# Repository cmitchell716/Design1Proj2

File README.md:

# Design1Proj2
This repository holds the source code for ECEN 4013 Group 2 Project 2.
The PCB and Case directories hold the files required for each component respectively. 
The headers directory have the modified header files in order to save memory.
Sketches hold all code run on the arduino, project_full is the final sketch used in the 
demonstration. All others test individual components or other related activities.

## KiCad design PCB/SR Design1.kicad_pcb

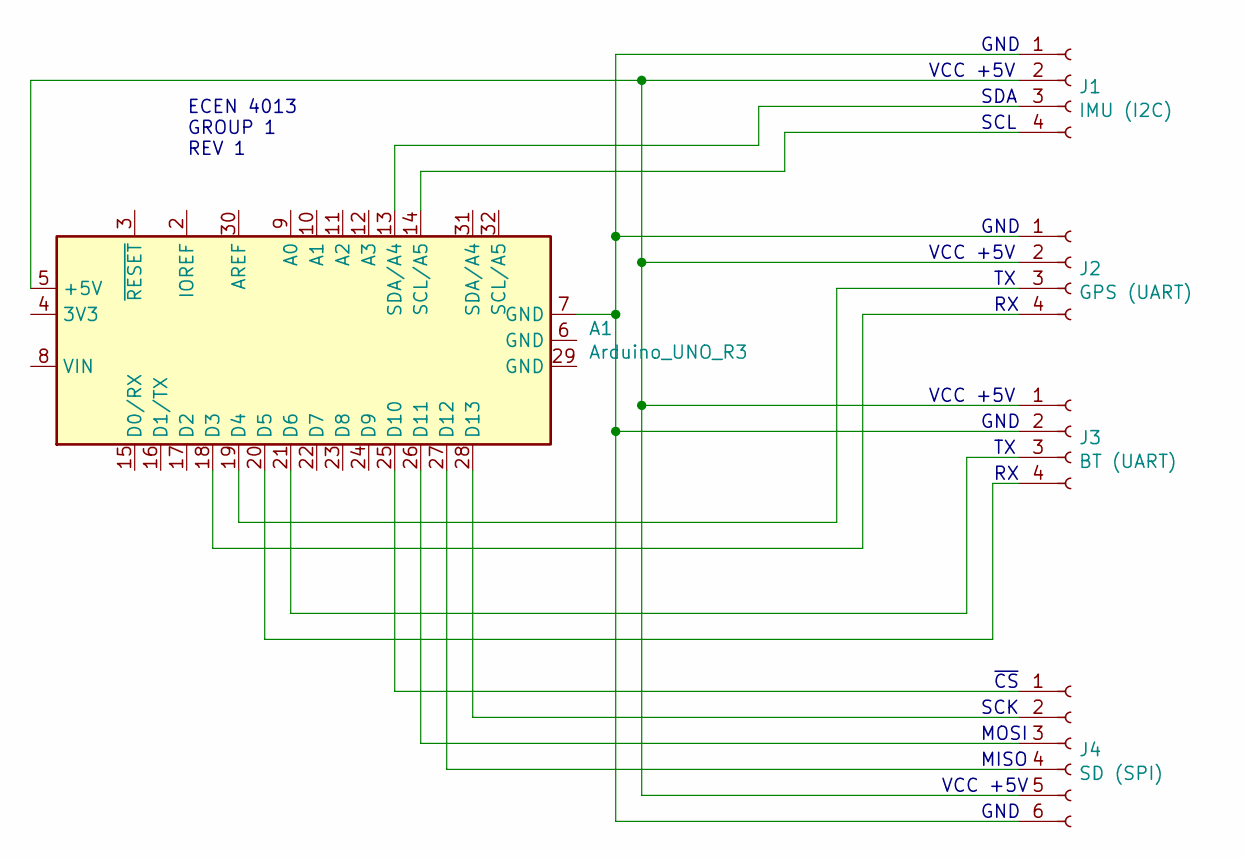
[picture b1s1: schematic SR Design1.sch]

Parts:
A1: Arduino_UNO_R3
J1: IMU (I2C); PinHeader_1x04_P1.00mm_Horizontal
J2: GPS (UART); PinHeader_1x04_P1.00mm_Horizontal
J3: BT (UART); PinSocket_1x04_P2.54mm_Horizontal
J4: SD (SPI); PinSocket_1x06_P2.54mm_Horizontal

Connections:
unnamed: A1.5 (+5V), J1.2, J2.2, J3.1, J4.5
unnamed: A1.7 (GND), J1.1, J2.1, J3.2, J4.6
unnamed: A1.13 (SDA/A4), J1.3
unnamed: A1.14 (SCL/A5), J1.4
unnamed: A1.18 (D3), J2.4
unnamed: A1.19 (D4), J2.3
unnamed: A1.20 (D5), J3.4
unnamed: A1.21 (D6), J3.3
unnamed: A1.25 (D10), J4.1
unnamed: A1.26 (D11), J4.3
unnamed: A1.27 (D12), J4.4
unnamed: A1.28 (D13), J4.2

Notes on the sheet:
GND
VCC +5V
SDA
SCL
SCK
MOSI
MISO
~CS
ECEN 4013 GROUP 1 REV 1

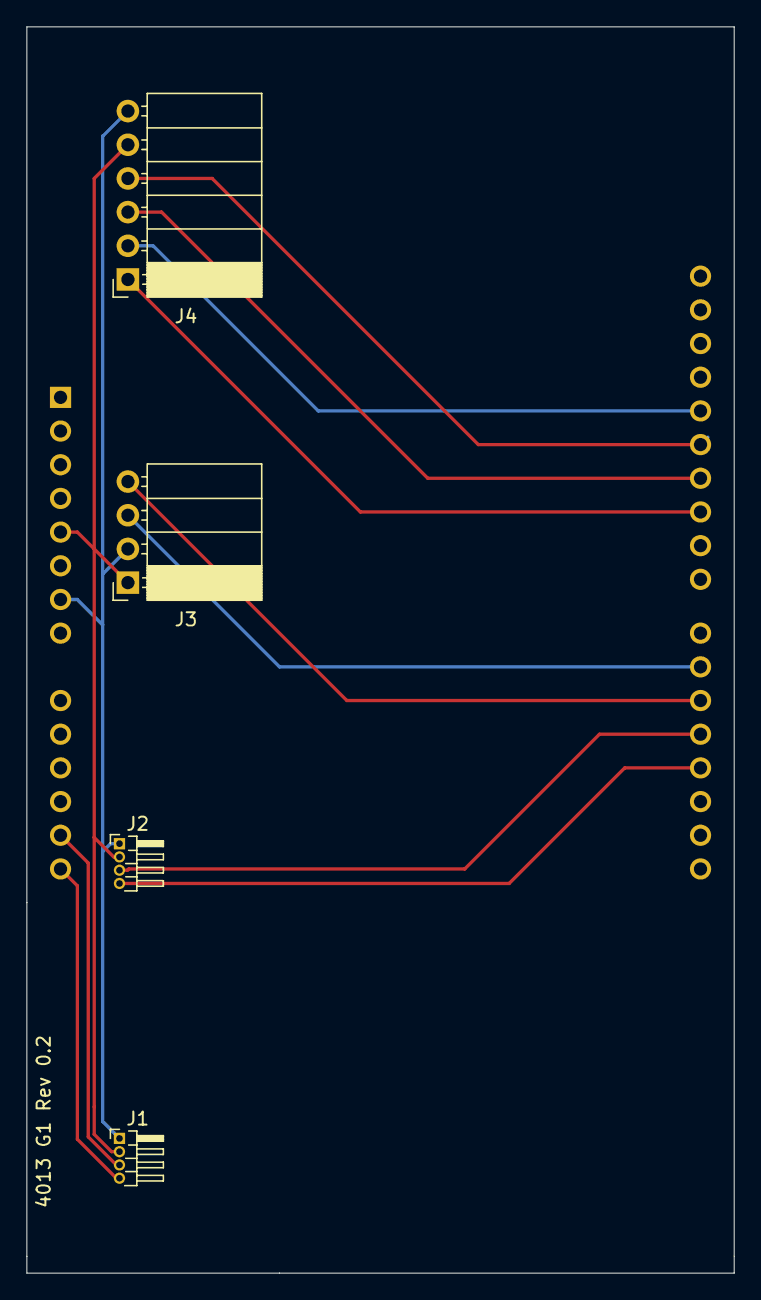
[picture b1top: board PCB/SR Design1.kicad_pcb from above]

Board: 2 copper layers, 53.3 x 94.0 mm, 5 parts (1 on the bottom side), 12 nets.

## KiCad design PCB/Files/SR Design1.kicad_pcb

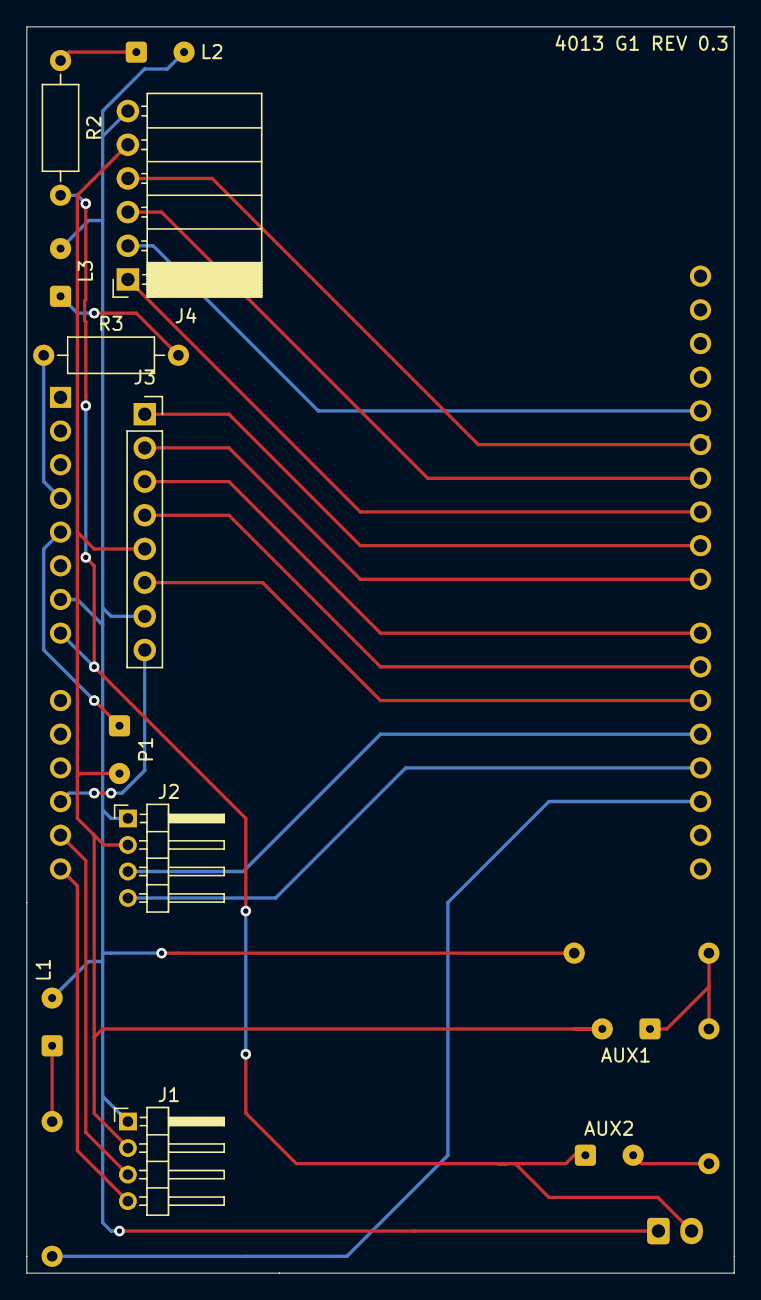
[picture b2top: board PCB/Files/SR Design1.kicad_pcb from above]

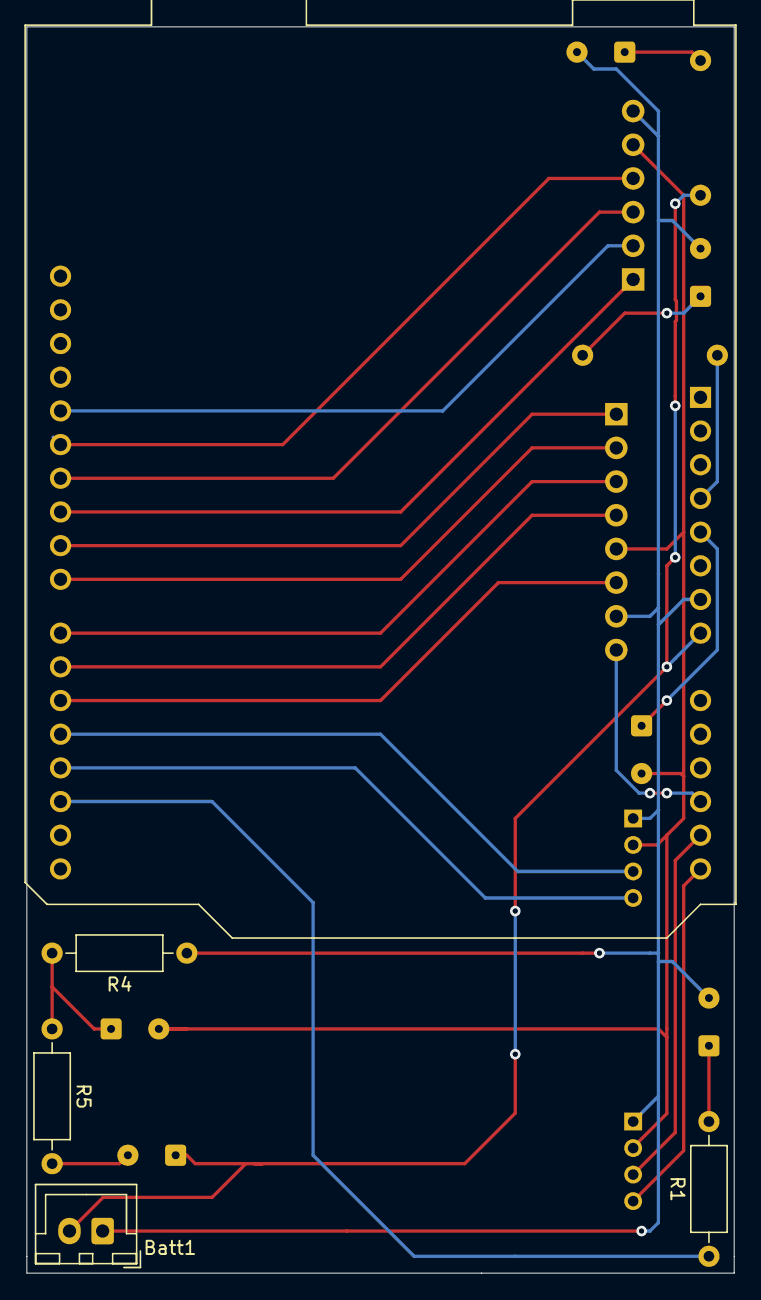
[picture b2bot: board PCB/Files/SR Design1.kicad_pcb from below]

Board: 2 copper layers, 53.3 x 94.0 mm, 17 parts (5 on the bottom side), 25 nets.

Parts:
A1: Arduino_UNO_R3
AUX1, AUX2: PWR; SolderWire-0.1sqmm_1x02_P3.6mm_D0.4mm_OD1mm
Batt1: PWR; JST_XH_B2B-XH-A_1x02_P2.50mm_Vertical
J1: IMU (I2C); PinHeader_1x04_P2.00mm_Horizontal
J2: GPS (UART); PinHeader_1x04_P2.00mm_Horizontal
J3: BT (UART +); PinSocket_1x08_P2.54mm_Vertical
J4: SD (SPI); PinSocket_1x06_P2.54mm_Horizontal
L1, L2, L3: LED; SolderWire-0.1sqmm_1x02_P3.6mm_D0.4mm_OD1mm
P1: PWR; SolderWire-0.1sqmm_1x02_P3.6mm_D0.4mm_OD1mm
R1, R2, R3: R227; R_Axial_DIN0207_L6.3mm_D2.5mm_P10.16mm_Horizontal
R4: R5k; R_Axial_DIN0207_L6.3mm_D2.5mm_P10.16mm_Horizontal
R5: R2.2k; R_Axial_DIN0207_L6.3mm_D2.5mm_P10.16mm_Horizontal

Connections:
unnamed: A1.4, R3.1
unnamed: A1.5, P1.1
unnamed: A1.7, Batt1.1, J1.1, J2.1, J3.7, J4.6, L1.2, L2.2, L3.2, R4.1
unnamed: A1.8, AUX2.1, Batt1.2, R2.1
unnamed: A1.12, J3.8
unnamed: A1.13, J1.3
unnamed: A1.14, J1.4
unnamed: A1.17, R1.1
unnamed: A1.18, J2.4
unnamed: A1.19, J2.3
unnamed: A1.20, J3.6
unnamed: A1.21, J3.4
unnamed: A1.22, J3.3
unnamed: A1.23, J3.2
unnamed: A1.24, J3.1
unnamed: A1.25, J4.1
unnamed: A1.26, J4.3
unnamed: A1.27, J4.4
unnamed: A1.28, J4.2
unnamed: AUX1.1, R4.2, R5.1
unnamed: AUX1.2, J1.2, J2.2, J3.5, J4.5, P1.2
unnamed: AUX2.2, R5.2
unnamed: L1.1, R1.2
unnamed: L2.1, R2.2
unnamed: L3.1, R3.2

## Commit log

2021-11-01 Adding PCB Files and Dir
    Adding the KiCad Files and supplementary file structure (Currently Using SVN - Trunk, Branch, Tag Structure. Can be changed later)
2021-11-02 add BT test sketch
2021-11-02 Revert "Adding PCB Files and Dir"
    This reverts commit 94645a1b65692bb09303bc4e4d5ecebb7ac4a380.
2021-11-03 Adding PCB Files
    Adds
    - fp-info-cache
    - Sr Design 1-cache.lib
    - Sr Design 1.kicad_pcb
    - Sr Design 1.kicad_pcb-bak
    - Sr Design 1.net
2021-11-03 IMU test, configuration, and I2C connection check
2021-11-03 Updated PCB to REV 0.3
    Updated all PCB files previously added. These should be updated to Rev 0.3 with new BT module and alternative power circuit. Board size not changed.
2021-11-03 Updated Schmatic
    Updated Schematic to the correct revision.
2021-11-04 Adding finished PCB and Gerber Files
    Added all Gerber files not in .zip form. Also updated PCB to newest version.
2021-11-05 GPS and Combined Input
2021-11-05 Added sd_test
2021-11-06 reduced storage space of IMU and fixed magnetometer
2021-11-09 strip header files for full sketch
2021-11-09 Changed buffer size for SD to 256
    To change the buffer further, look at lines 69 and 182.
2021-11-10 project_full outputs blutooth and serial
2021-11-12 Adding Case Files
    Adding SolidWorks files and STL files of our case.
2021-11-12 full implementation without testing bluetooth
2021-11-15 Bluetooth working with some data loss
2021-11-16 final code fingers crossed
2021-11-17 Update fp-info-cache
2021-11-17 Moved KiCad Files
    Moved KiCad Files and added a .txt file illustrating new wiring for power.
2021-11-18 All nighters
